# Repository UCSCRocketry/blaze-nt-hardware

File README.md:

# Blaze-NT Avionics System

UCSC Rocketry's high-power rocket flight computer and data acquisition system.

## Overview

The Blaze-NT is a complete avionics system designed for high-power rocket
applications. It provides flight data logging, sensor monitoring, and telemetry
capabilities for UCSC Rocketry team's launch vehicles.

**Current Status**: Prototype hardware has been flight-tested. This repository
contains the schematic revision for the next hardware iteration.

## Features

- **Flight Data Logging**: High-rate sensor data acquisition and storage
- **Telemetry**: 433MHz radio communication for real-time data downlink
- **Sensor Suite**:
  - 9-axis IMU (accelerometer, gyroscope, magnetometer)
  - Barometric pressure sensor for altitude
  - Discrete accelerometer for high-g measurements
- **Power Management**: Battery monitoring and regulated power distribution
- **Microcontroller**: STM32F411 ARM Cortex-M4 processor
- **Firmware**: Arduino framework compatibility

## Project Structure

This KiCad project uses a hierarchical schematic design with separate sheets for
each subsystem:

```
Blaze-NT/
├── Blaze-NT.kicad_sch          # Top-level schematic (team lead managed)
├── microcontroller.kicad_sch   # STM32F411 and peripherals (team lead managed)
├── power-managment.kicad_sch   # Power regulation and distribution (power team)
├── sensors.kicad_sch           # Sensor interfaces and signal conditioning (sensors team)
├── Radio.kicad_sch             # 433MHz telemetry radio (radio team)
├── Blaze-NT.kicad_pro          # Project file
├── avionics-library/           # Custom component library (git submodule)
└── README.md
```

## Hardware Components

### Main Processor

- **STM32F411**: ARM Cortex-M4 microcontroller running the Arduino framework

### Radio System

- **433MHz Transceiver**: RFM69HCW for telemetry communication
- **Antenna**: External 433MHz antenna connector

### Sensors

- **IMU**: LSM9DS1 9-axis inertial measurement unit
- **Barometer**: MS5611 high-precision pressure sensor
- **High-G Accelerometer**: KX134 for high-acceleration events

### Power Management

- **Voltage Regulators**: Integreated bucks for efficient power conversion
- **Battery Monitoring**: Voltage and current sensing capabilities

## Development Workflow

### Team-Based Development

This project is designed for collaborative development with the following roles:

**Team Lead Responsibilities:**

- Manages top-level schematic (`Blaze-NT.kicad_sch`)
- Manages microcontroller sheet (`microcontroller.kicad_sch`)
- Coordinates integration between subsystems
- Handles final schematic review and approval

**Subteam Responsibilities:**

- **Power Team**: Works on `power-managment.kicad_sch`
- **Sensors Team**: Works on `sensors.kicad_sch`
- **Radio Team**: Works on `Radio.kicad_sch`
- Each team only modifies their assigned schematic sheet

### Version Control Notes

**Important**: KiCad schematic files are binary and do not merge well. When
conflicts occur:

1. **Latest Version Wins**: The newest schematic file will override older
   versions in merges
2. **Communication is Key**: Teams must coordinate changes to avoid overwriting
   work
3. **Branch Strategy**: Use feature branches for significant changes
4. **Regular Integration**: Team lead regularly integrates subteam changes

#### Resolving Merge Conflicts with Schematics

When pulling changes from main and conflicts occur in schematic files, you may need to choose which version to keep:

**To keep your branch's version of a schematic:**

```bash
# After git pull results in conflicts
git checkout --ours <schematic-file>.kicad_sch
git add <schematic-file>.kicad_sch
git commit -m "Resolve merge conflict: keep branch version of <schematic-file>"
```

**To keep the main branch's version of a schematic:**

```bash
# After git pull results in conflicts  
git checkout --theirs <schematic-file>.kicad_sch
git add <schematic-file>.kicad_sch
git commit -m "Resolve merge conflict: use main version of <schematic-file>"
```

**Example for power team keeping their version:**

```bash
git checkout --ours power-managment.kicad_sch
git add power-managment.kicad_sch
git commit -m "Resolve merge conflict: keep branch version of power-managment schematic"
```

**Important**: Always communicate with the team lead before resolving conflicts to ensure important changes aren't lost.

### Git Workflow

```bash
# Clone with submodules
git clone --recurse-submodules <repository-url>

# Or initialize submodules after cloning
git submodule update --init --recursive

# Create feature branch for subsystem changes
git checkout -b feature/power-improvements

# Make changes to your assigned sheet only
# Commit and push changes
git add power-managment.kicad_sch
git commit -m "Improve power regulation efficiency"
git push origin feature/power-improvements
```

## Build Instructions

### Prerequisites

- KiCad 9.0 or later
- Git for version control

### Opening the Project

1. Clone the repository with submodules:
   ```bash
   git clone --recurse-submodules https://github.com/UCSCRocketry/blaze-nt-hardware.git
   ```

2. Open KiCad
3. Open the project file: `Blaze-NT.kicad_pro`

### Working with Schematics

1. **Team Lead**: Open and edit `Blaze-NT.kicad_sch` and
   `microcontroller.kicad_sch`
2. **Subteams**: Open only your assigned schematic sheet
3. **Symbol Library**: Custom symbols are in
   `avionics-library/Avionics_Symbols.kicad_sym`
4. **Footprints**: Custom footprints are in
   `avionics-library/Avionics_Feet.pretty/`

## Component Library

This project uses a custom component library stored as a git submodule:

- **Repository**: `UCSCRocketry/avionics-library`
- **Symbols**: `avionics-library/Avionics_Symbols.kicad_sym`
- **Footprints**: `avionics-library/Avionics_Feet.pretty/`

To update the library:

```bash
git submodule update --remote avionics-library
git add avionics-library
git commit -m "Update avionics library"
```

## Contribution Guidelines

### For Subteams

1. **Stay in Your Lane**: Only modify your assigned schematic sheet
2. **Test Changes**: Verify electrical rules check (ERC) passes before
   committing
3. **Document Changes**: Update schematic notes and component values
4. **Coordinate**: Communicate with team lead before major changes

### For Team Lead

1. **Review Changes**: Check all subteam contributions before integration
2. **Maintain Top Sheet**: Update hierarchical sheet references as needed
3. **Version Control**: Manage merge conflicts and coordinate integration
4. **Quality Control**: Ensure overall schematic integrity and consistency

### Commit Message Format

Use clear, descriptive commit messages:

```
subsystem: brief description

Detailed explanation of changes if needed.
```

Examples:

- `power: add battery voltage monitoring`
- `sensors: update IMU filter configuration`
- `radio: improve antenna matching network`

## File Formats

- **Schematics**: `.kicad_sch` (binary format)
- **Project Settings**: `.kicad_pro` (JSON format)
- **Project Local**: `.kicad_prl` (local settings, gitignored)
- **Symbol Library**: `.kicad_sym` (binary format)
- **Footprints**: `.kicad_mod` (text format)

## Troubleshooting

### Common Issues

1. **Missing Symbols**: Ensure `avionics-library` submodule is initialized
2. **Schematic Won't Open**: Check KiCad version compatibility
3. **ERC Errors**: Review net connections and component properties

### Getting Help

- Contact the project team lead for integration issues
- Consult KiCad documentation for tool-specific questions
- Review existing schematic sheets for design patterns

## License

This project is proprietary to UCSC Rocketry team. Do not distribute without
permission.

---

**Note**: This hardware has been flight-tested on prototype vehicles. Always
perform thorough ground testing before flight use.

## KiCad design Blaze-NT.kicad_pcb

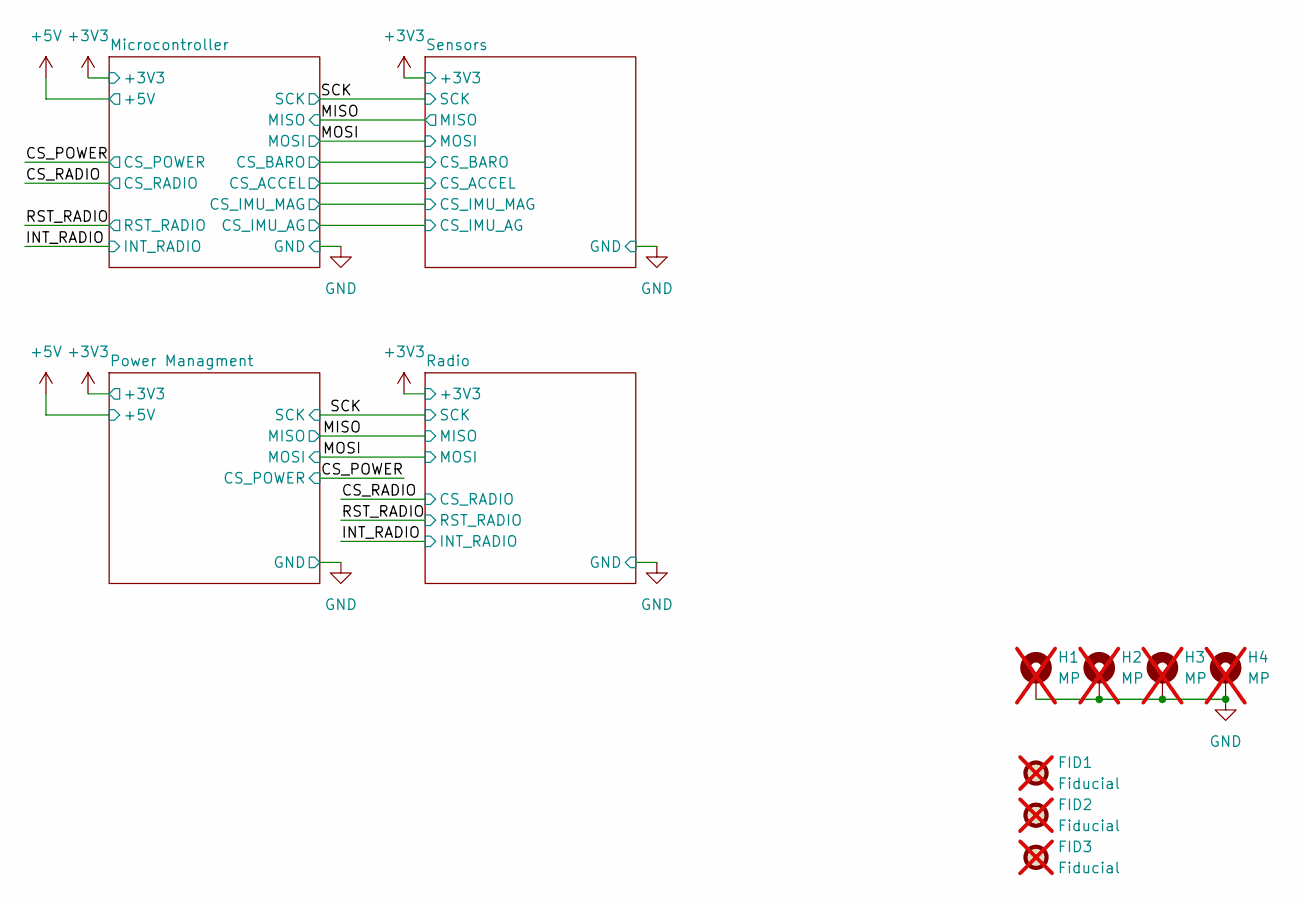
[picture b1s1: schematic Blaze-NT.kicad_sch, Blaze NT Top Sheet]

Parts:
FID1, FID2, FID3: Fiducial; JLC_Fiducial; not fitted
H1, H2, H3, H4: MP; MountingHole_3.2mm_M3_ISO7380_Pad; not fitted

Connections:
GND: H1.1, H2.1, H3.1, H4.1; also elsewhere on the board

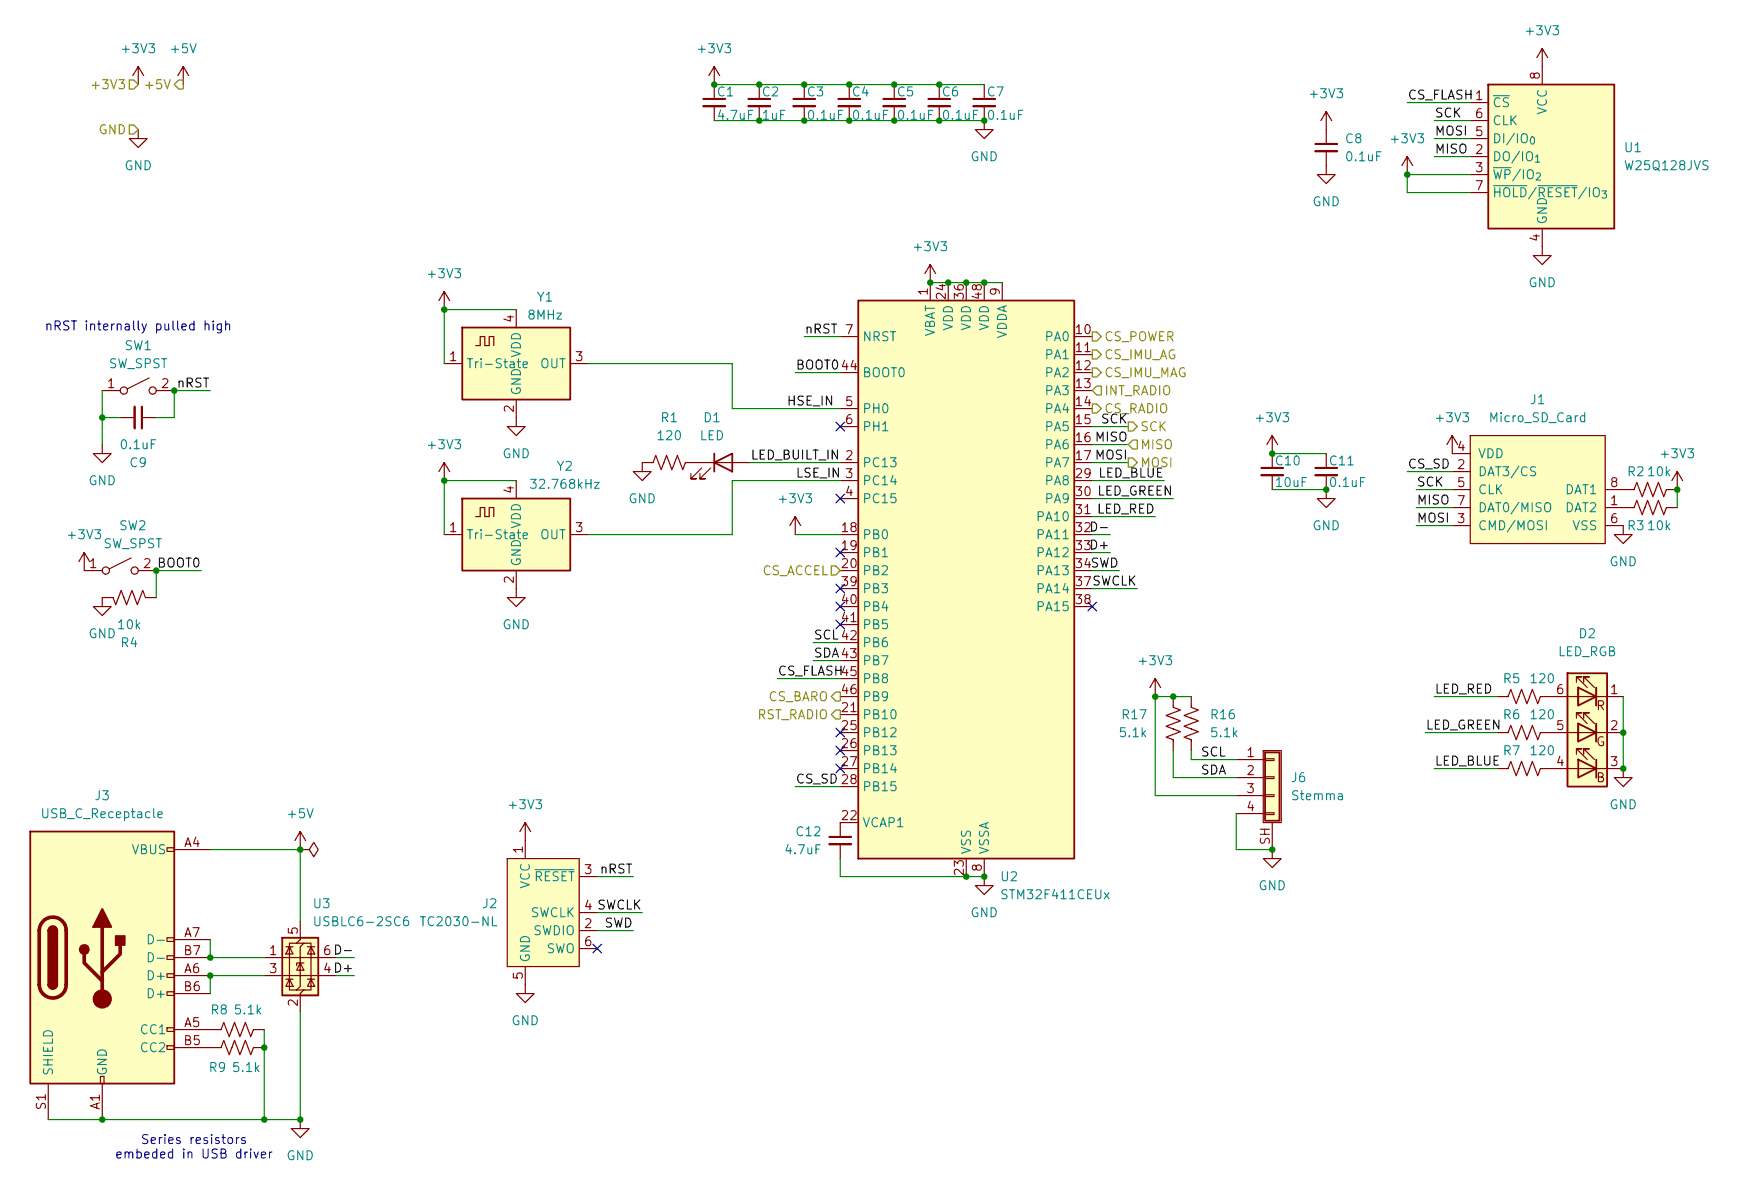
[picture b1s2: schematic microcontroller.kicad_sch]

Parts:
C1, C12: 4.7uF; C_0603_1608Metric; LCSC C19666
C2: 1uF; C_0603_1608Metric; LCSC C15849
C3, C4, C5, C6, C7, C8, C9, C11: 0.1uF; C_0603_1608Metric; LCSC C14663
C10: 10uF; C_0603_1608Metric; LCSC C96446
D1: LED; LED_0603_1608Metric; LCSC C2994781
D2: LED_RGB; LED_RGB_5050-6; LCSC C784540
J1: Micro_SD_Card; microSD_HC_Molex_47219-2001
J2: TC2030-NL; Tag-Connect_TC2030-IDC-NL_2x03_P1.27mm_Vertical
J3: USB_C_Receptacle; USB_C_Receptacle_GCT_USB4105-xx-A_16P_TopMnt_Horizontal; LCSC C3025063
J6: Stemma; JST_SH_SM04B-SRSS-TB_1x04-1MP_P1.00mm_Horizontal; LCSC C160404
R1, R5, R6, R7: 120; R_0603_1608Metric; LCSC C22787
R2, R3, R4: 10k; R_0603_1608Metric; LCSC C98220
R8, R9, R16, R17: 5.1k; R_0603_1608Metric; LCSC C2907044
SW1, SW2: SW_SPST; SW_SPST_B3U-1000P-B; LCSC C231329
U1: W25Q128JVS; SOIC-8_5.3x5.3mm_P1.27mm; LCSC C97521
U2: STM32F411CEUx; QFN-48-1EP_7x7mm_P0.5mm_EP5.6x5.6mm; LCSC C60420
U3: USBLC6-2SC6; SOT-23-6; LCSC C7519
Y1: 8MHz; Oscillator_SMD_Abracon_ASCO-4Pin_1.6x1.2mm; LCSC ASCO-8.000MHZ-EK-T3
Y2: 32.768kHz; Oscillator_SMD_Abracon_ASCO-4Pin_1.6x1.2mm; Digikey 50-ECS-327MV-CN-TRCT-ND

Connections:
+3V3: C1.1, C2.1, C3.1, C4.1, C5.1, C6.1, C7.1, C8.1, C10.1, C11.1, J1.4 (VDD), J2.1 (VCC), J6.3, R2.2, R3.2, R16.1, R17.1, SW2.1 (A), U1.3 (~WP/IO_{2}), U1.7 (~HOLD/~RESET/IO_{3}), U1.8 (VCC), U2.1 (VBAT), U2.9 (VDDA), U2.18 (PB0), U2.24 (VDD), U2.36 (VDD), U2.48 (VDD), Y1.1 (Tri-State), Y1.4 (VDD), Y2.1 (Tri-State), Y2.4 (VDD); also elsewhere on the board
+5V: J3.A4 (VBUS), J3.A9 (VBUS), J3.B4 (VBUS), J3.B9 (VBUS), U3.5 (VBUS); also elsewhere on the board
/CS_POWER: U2.10 (PA0); also elsewhere on the board
/CS_RADIO: U2.14 (PA4); also elsewhere on the board
/INT_RADIO: U2.13 (PA3); also elsewhere on the board
/MISO: J1.7 (DAT0/MISO), U1.2 (DO/IO_{1}), U2.16 (PA6); also elsewhere on the board
/MOSI: J1.3 (CMD/MOSI), U1.5 (DI/IO_{0}), U2.17 (PA7); also elsewhere on the board
/Microcontroller/BOOT0: R4.2, SW2.2 (B), U2.44 (BOOT0)
/Microcontroller/CS_ACCEL: U2.20 (PB2); also elsewhere on the board
/Microcontroller/CS_BARO: U2.46 (PB9); also elsewhere on the board
/Microcontroller/CS_FLASH: U1.1 (~CS), U2.45 (PB8)
/Microcontroller/CS_IMU_AG: U2.11 (PA1); also elsewhere on the board
/Microcontroller/CS_IMU_MAG: U2.12 (PA2); also elsewhere on the board
/Microcontroller/CS_SD: J1.2 (DAT3/CS), U2.28 (PB15)
/Microcontroller/D+: U2.33 (PA12), U3.4 (I/O2)
/Microcontroller/D-: U2.32 (PA11), U3.6 (I/O1)
/Microcontroller/HSE_IN: U2.5 (PH0), Y1.3 (OUT)
/Microcontroller/LED_BLUE: R7.1, U2.29 (PA8)
/Microcontroller/LED_BUILT_IN: D1.2 (A), U2.2 (PC13)
/Microcontroller/LED_GREEN: R6.1, U2.30 (PA9)
/Microcontroller/LED_RED: R5.1, U2.31 (PA10)
/Microcontroller/LSE_IN: U2.3 (PC14), Y2.3 (OUT)
/Microcontroller/SCL: J6.1, R16.2, U2.42 (PB6)
/Microcontroller/SDA: J6.2, R17.2, U2.43 (PB7)
/Microcontroller/SWCLK: J2.4 (SWCLK), U2.37 (PA14)
/Microcontroller/SWD: J2.2 (SWDIO), U2.34 (PA13)
/Microcontroller/nRST: C9.1, J2.3 (~RESET), SW1.2 (B), U2.7 (NRST)
/RST_RADIO: U2.21 (PB10); also elsewhere on the board
/SCK: J1.5 (CLK), U1.6 (CLK), U2.15 (PA5); also elsewhere on the board
GND: C1.2, C2.2, C3.2, C4.2, C5.2, C6.2, C7.2, C8.2, C9.2, C10.2, C11.2, C12.2, D2.1 (RK), D2.2 (GK), D2.3 (BK), J1.6 (VSS), J1.SHIELD (GND), J2.5 (GND), J3.A1 (GND), J3.A12 (GND), J3.B1 (GND), J3.B12 (GND), J3.S1 (SHIELD), J6.4, J6.SH (Shield), R1.1, R4.1, R8.2, R9.2, SW1.1 (A), U1.4 (GND), U2.8 (VSSA), U2.23 (VSS), U2.35 (VSS), U2.47 (VSS), U2.49 (VSS), U3.2 (GND), Y1.2 (GND), Y2.2 (GND); also elsewhere on the board
unnamed: D1.1 (K), R1.2
unnamed: D2.4 (BA), R7.2
unnamed: D2.5 (GA), R6.2
unnamed: D2.6 (RA), R5.2
unnamed: J1.8 (DAT1), R2.1
unnamed: J1.1 (DAT2), R3.1
unnamed: J3.A5 (CC1), R8.1
unnamed: J3.B5 (CC2), R9.1
unnamed: J3.A6 (D+), J3.B6 (D+), U3.3 (I/O2)
unnamed: J3.A7 (D-), J3.B7 (D-), U3.1 (I/O1)
unnamed: C12.1, U2.22 (VCAP1)

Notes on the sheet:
nRST internally pulled high
Series resistors embeded in USB driver

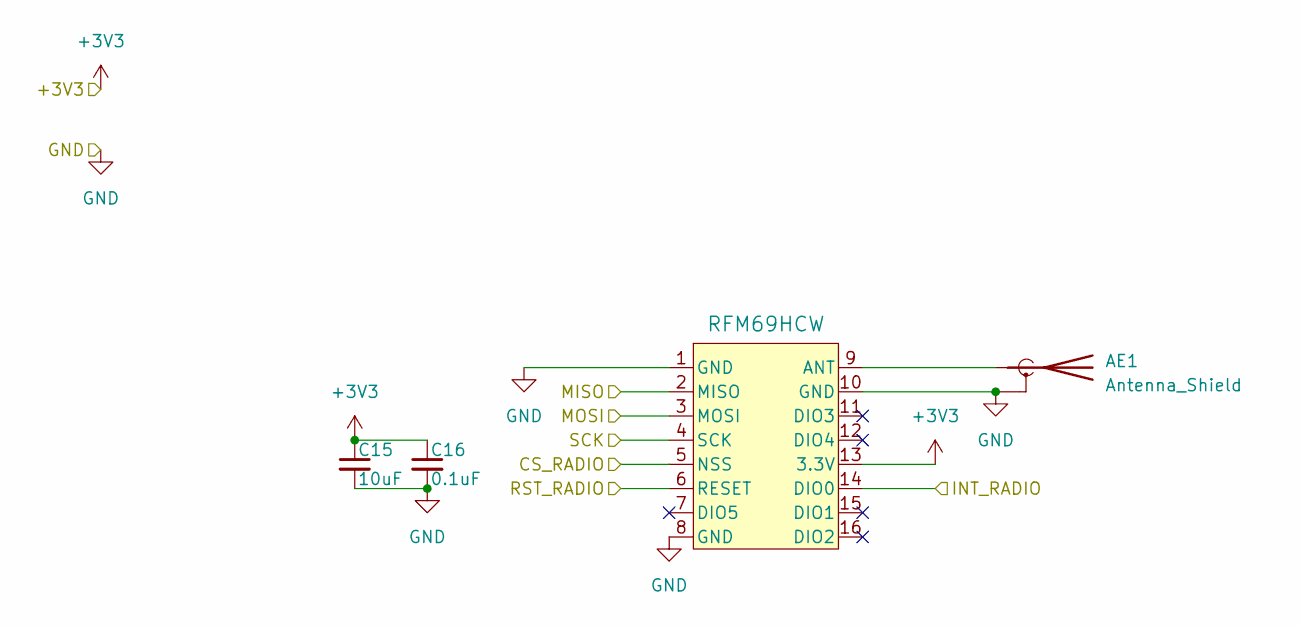
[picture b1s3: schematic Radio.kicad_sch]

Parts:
AE1: Antenna_Shield; SMA_Samtec_SMA-J-P-H-ST-EM1_EdgeMount; LCSC C5199907
C15: 10uF; C_0603_1608Metric; LCSC C96446
C16: 0.1uF; C_0603_1608Metric; LCSC C14663
U5: RFM69HCW; HOPERF_RFM9XW_SMD; LCSC C2844474

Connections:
+3V3: C15.1, C16.1, U5.13 (3.3V); also elsewhere on the board
/CS_RADIO: U5.5 (NSS); also elsewhere on the board
/INT_RADIO: U5.14 (DIO0); also elsewhere on the board
/MISO: U5.2 (MISO); also elsewhere on the board
/MOSI: U5.3 (MOSI); also elsewhere on the board
/RST_RADIO: U5.6 (RESET); also elsewhere on the board
/SCK: U5.4 (SCK); also elsewhere on the board
GND: AE1.2 (Shield), C15.2, C16.2, U5.1 (GND), U5.8 (GND), U5.10 (GND); also elsewhere on the board
unnamed: AE1.1 (A), U5.9 (ANT)

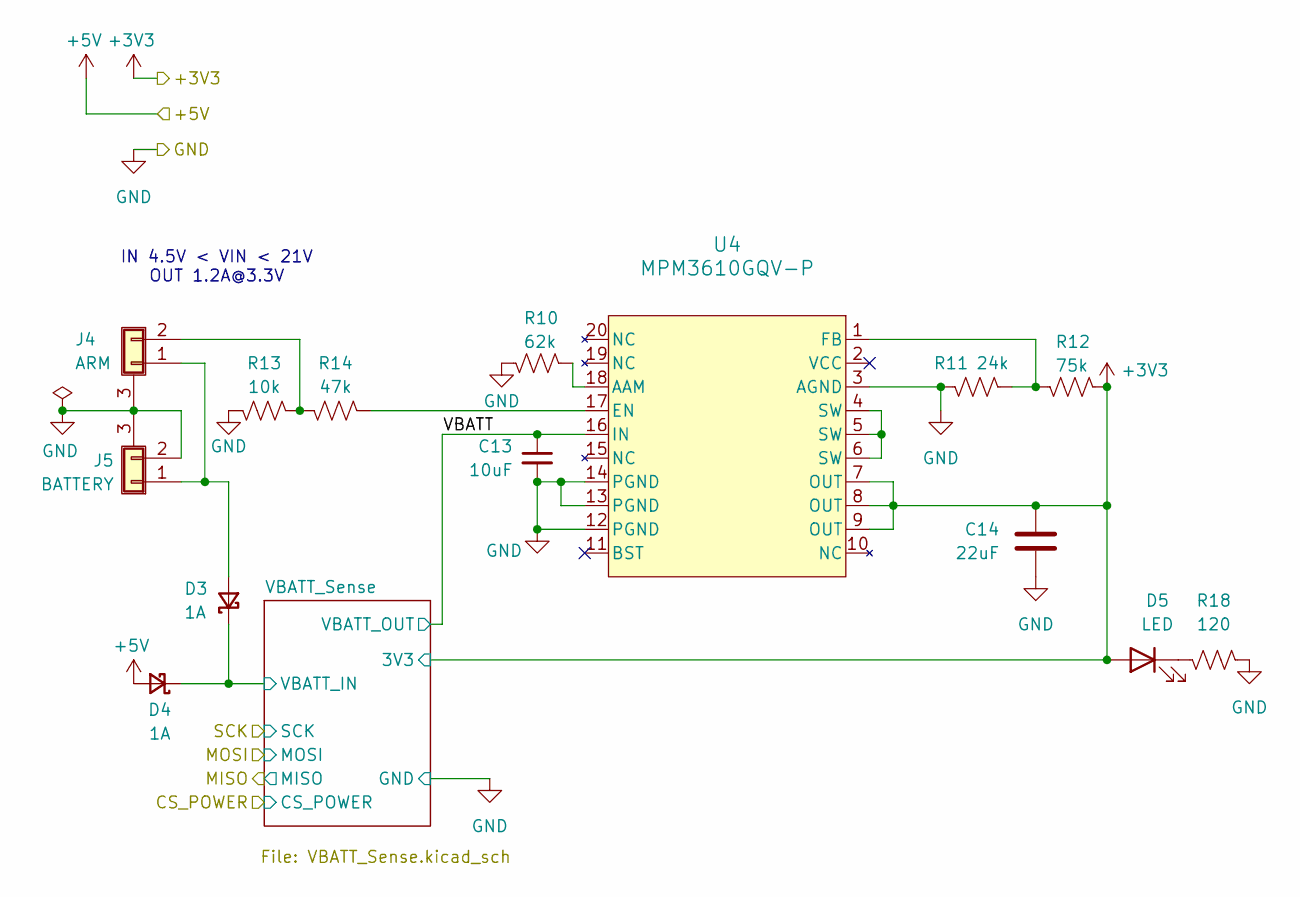
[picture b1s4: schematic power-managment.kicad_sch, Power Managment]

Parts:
C13: 10uF; C_0603_1608Metric; LCSC C96446
C14: 22uF; C_0603_1608Metric; LCSC C59461
D3, D4: 1A; D_SOD-123F; LCSC C784540
D5: LED; LED_0603_1608Metric; LCSC C2994781
J4: ARM; 0436500205; Digikey WM17581-ND
J5: BATTERY; 0436500205; Digikey WM17581-ND
R10: 62k; R_0603_1608Metric; LCSC C137694
R11: 24k; R_0603_1608Metric; LCSC C137760
R12: 75k; R_0603_1608Metric; LCSC C114636
R13: 10k; R_0603_1608Metric; LCSC C98220
R14: 47k; R_0603_1608Metric; LCSC C105579
R18: 120; R_0603_1608Metric; LCSC C22787
U4: MPM3610GQV-P; MPM3610QGV-P; Digikey 1589-1250-1-ND

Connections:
+3V3: C14.1, D5.2 (A), R12.1, U4.7 (OUT), U4.8 (OUT), U4.9 (OUT); also elsewhere on the board
+5V: D4.2 (A); also elsewhere on the board
/Power Managment/VBATT: C13.1, U4.16 (IN); also elsewhere on the board
/Power Managment/VBATT_Sense/VBATT_IN: D3.1 (K), D4.1 (K); also elsewhere on the board
GND: C13.2, C14.2, J4.3 (Shield), J5.2, J5.3 (Shield), R10.1, R11.2, R13.2, R18.1, U4.3 (AGND), U4.12 (PGND), U4.13 (PGND), U4.14 (PGND); also elsewhere on the board
unnamed: D3.2 (A), J4.1 (Pin_2), J5.1
unnamed: D5.1 (K), R18.2
unnamed: J4.2 (Pin_1), R13.1, R14.2
unnamed: R10.2, U4.18 (AAM)
unnamed: R14.1, U4.17 (EN)
unnamed: R11.1, R12.2, U4.1 (FB)
unnamed: U4.4 (SW), U4.5 (SW), U4.6 (SW)

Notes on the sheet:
IN 4.5V < VIN < 21V OUT 1.2A@3.3V

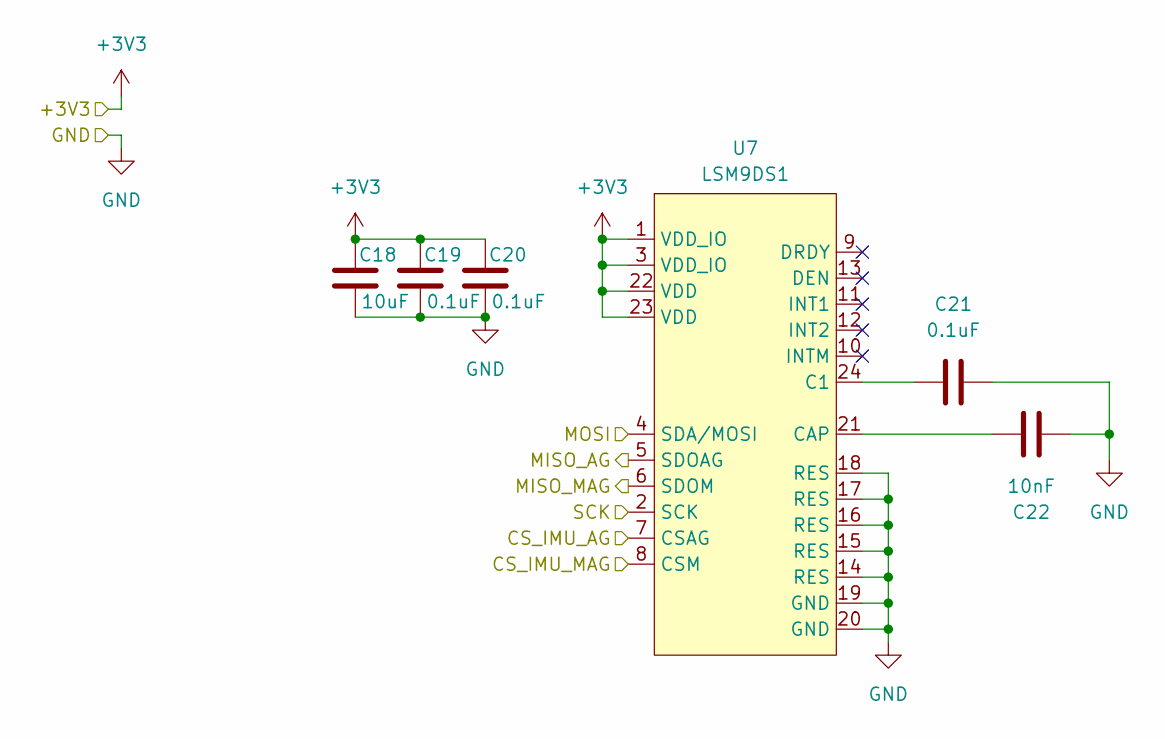
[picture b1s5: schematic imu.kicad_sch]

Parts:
C18: 10uF; C_0603_1608Metric; LCSC C96446
C19, C20, C21: 0.1uF; C_0603_1608Metric; LCSC C14663
C22: 10nF; C_0603_1608Metric; LCSC C1589
U7: LSM9DS1; PQFN24P43_350X300X102L35X23N; LCSC C2655096

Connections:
+3V3: C18.1, C19.1, C20.1, U7.1 (VDD_IO), U7.3 (VDD_IO), U7.22 (VDD), U7.23 (VDD); also elsewhere on the board
/MISO: U7.5 (SDOAG), U7.6 (SDOM); also elsewhere on the board
/MOSI: U7.4 (SDA/MOSI); also elsewhere on the board
/Microcontroller/CS_IMU_AG: U7.7 (CSAG); also elsewhere on the board
/Microcontroller/CS_IMU_MAG: U7.8 (CSM); also elsewhere on the board
/SCK: U7.2 (SCK); also elsewhere on the board
GND: C18.2, C19.2, C20.2, C21.1, C22.2, U7.14 (RES), U7.15 (RES), U7.16 (RES), U7.17 (RES), U7.18 (RES), U7.19 (GND), U7.20 (GND); also elsewhere on the board
unnamed: C21.2, U7.24 (C1)
unnamed: C22.1, U7.21 (CAP)

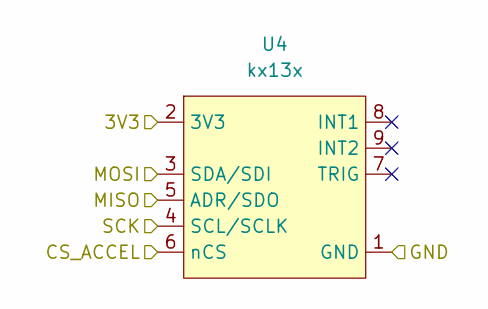
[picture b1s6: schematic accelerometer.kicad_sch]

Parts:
U4: kx13x

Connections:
+3V3: U4.7 (OUT), U4.8 (OUT), U4.9 (OUT); also elsewhere on the board
GND: U4.3 (AGND); also elsewhere on the board
unnamed 49: U4.1 (FB); also elsewhere on the board
unnamed: U4.4 (SW), U4.5 (SW), U4.6 (SW)

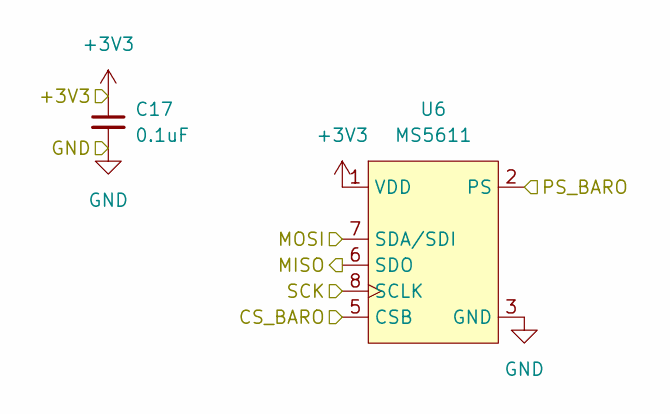
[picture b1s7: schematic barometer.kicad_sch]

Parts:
C17: 0.1uF; C_0603_1608Metric; LCSC C14663
U6: MS5611; XDCR_MS561101BA03-50; LCSC C15639

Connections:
+3V3: C17.1, U6.1 (VDD); also elsewhere on the board
/MISO: U6.6 (SDO); also elsewhere on the board
/MOSI: U6.7 (SDA/SDI); also elsewhere on the board
/Microcontroller/CS_BARO: U6.4 (CSB), U6.5 (CSB); also elsewhere on the board
/SCK: U6.8 (SCLK); also elsewhere on the board
GND: C17.2, U6.2 (PS), U6.3 (GND); also elsewhere on the board

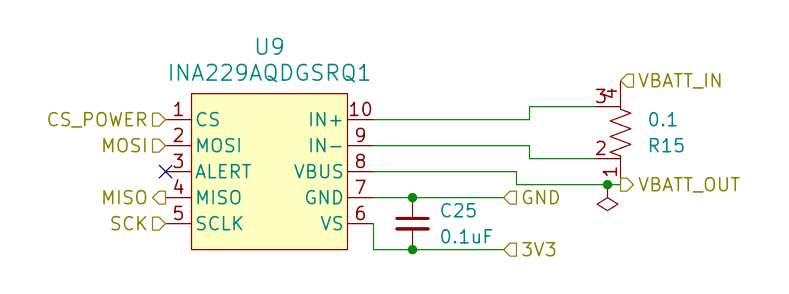
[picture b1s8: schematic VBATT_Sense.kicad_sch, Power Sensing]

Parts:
C25: 0.1uF; C_0603_1608Metric; LCSC C14663
R15: 0.1; R_Shunt_Ohmite_LVK24; LCSC C6981159
U9: INA229AQDGSRQ1; VSSOP-10_3x3mm_P0.5mm; LCSC C2870151

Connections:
+3V3: C25.2, U9.6 (VS); also elsewhere on the board
/CS_POWER: U9.1 (CS); also elsewhere on the board
/MISO: U9.4 (MISO); also elsewhere on the board
/MOSI: U9.2 (MOSI); also elsewhere on the board
/Power Managment/VBATT: R15.1, U9.8 (VBUS); also elsewhere on the board
/Power Managment/VBATT_Sense/VBATT_IN: R15.4; also elsewhere on the board
/SCK: U9.5 (SCLK); also elsewhere on the board
GND: C25.1, U9.7 (GND); also elsewhere on the board
unnamed: R15.3, U9.10 (IN+)
unnamed: R15.2, U9.9 (IN-)

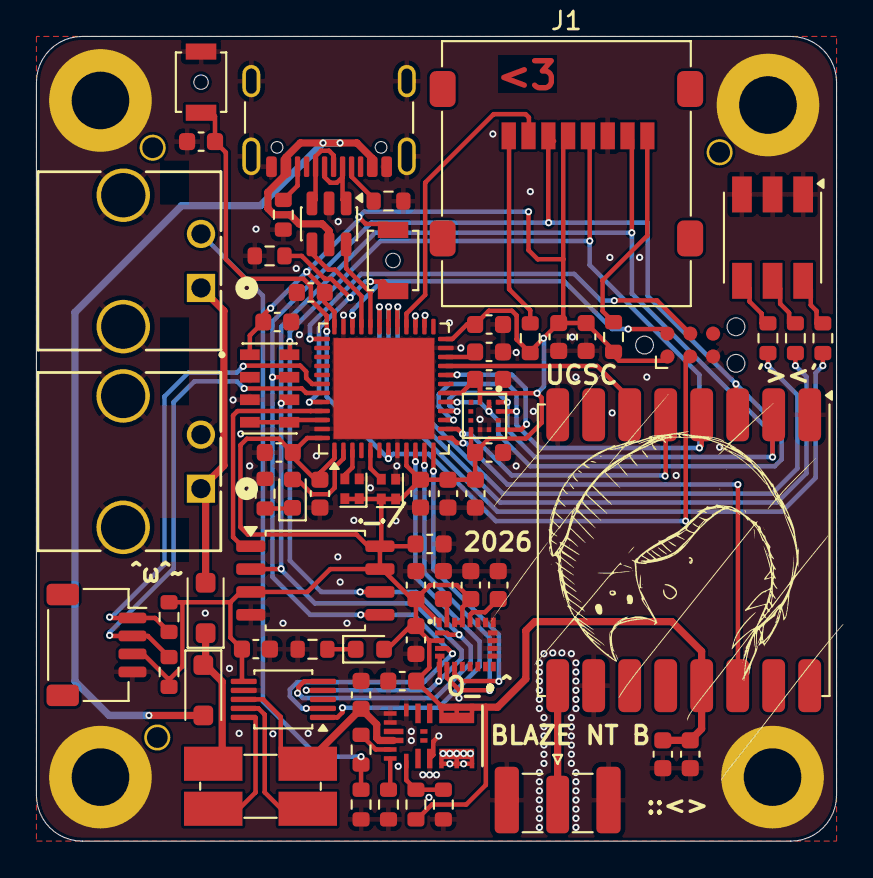
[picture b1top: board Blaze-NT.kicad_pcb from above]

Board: 2 copper layers, 44.4 x 44.7 mm, 75 parts (0 on the bottom side), 55 nets.

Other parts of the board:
C23, C24: 0.1uF; C_0603_1608Metric
U8: kx13x; XDCR_KX003-1077

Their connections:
+3V3: C23.1, C24.1, U8.3 (IO_VDD), U8.7 (VDD); also elsewhere on the board
/MISO: U8.1 (ADR/SDO); also elsewhere on the board
/MOSI: U8.2 (SDA/SDI); also elsewhere on the board
/Microcontroller/CS_ACCEL: U8.10 (nCS); also elsewhere on the board
/SCK: U8.12 (SCL/SCLK); also elsewhere on the board
GND: C23.2, C24.2, U8.8 (GND), U8.9 (GND), U8.11 (NC); also elsewhere on the board

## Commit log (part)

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2026-01-18 Schematic Sheet Setup
2026-01-18 Added symbol library submodule
2026-01-18 Added names to sheets
2026-01-19 MCU Schem capture
2026-01-19 Added bulk capacitnace
2026-01-19 Microcontroller topsheet
2026-01-19 Wrote README
2026-01-20 Updated heiarchal power labels
2026-01-20 Moved labels, updated USB conn symbol
2026-01-23 add subsheets to Sensors
2026-01-23 update sensors sheet
2026-01-23 Fixed MOSI/MISO on SD
2026-01-23 update sensors
2026-01-25 Add battery for git testing
2026-01-26 MPM3610 Power Buck Added
2026-01-26 Updated avionics library
2026-01-26 Julia cleaning wires
2026-01-26 meow
2026-01-29 Add MPM3610 Footprint
2026-01-29 save changes
2026-01-29 add radio branch
2026-01-30 Update resistors
2026-02-02 Avi lib update
2026-02-02 README updates
2026-02-02 :README updates
2026-02-05 Merged sensors topsheet
2026-02-05 Merges schematics, did annotation
2026-02-05 Added IMU schematic
2026-02-05 Reannotated
2026-02-05 Connected topsheet
2026-02-05 Fixed ERC issues
2026-02-05 Footprint selection
2026-02-06 Merged radio
2026-02-06 Connected radio
2026-02-06 Radio footprint selection
2026-02-07 PCB work
2026-02-07 KX footprint
2026-02-11 Silk updates
2026-02-11 Addeed part numbers
2026-02-11 Added prod files
2026-02-17 PCB revisions
2026-02-18 Added fiducials
2026-02-18 Added Digikey Components
2026-04-02 random
2026-04-08 Updated to latest version of avionics library
2026-04-08 Updated SD card to corrected symbol
